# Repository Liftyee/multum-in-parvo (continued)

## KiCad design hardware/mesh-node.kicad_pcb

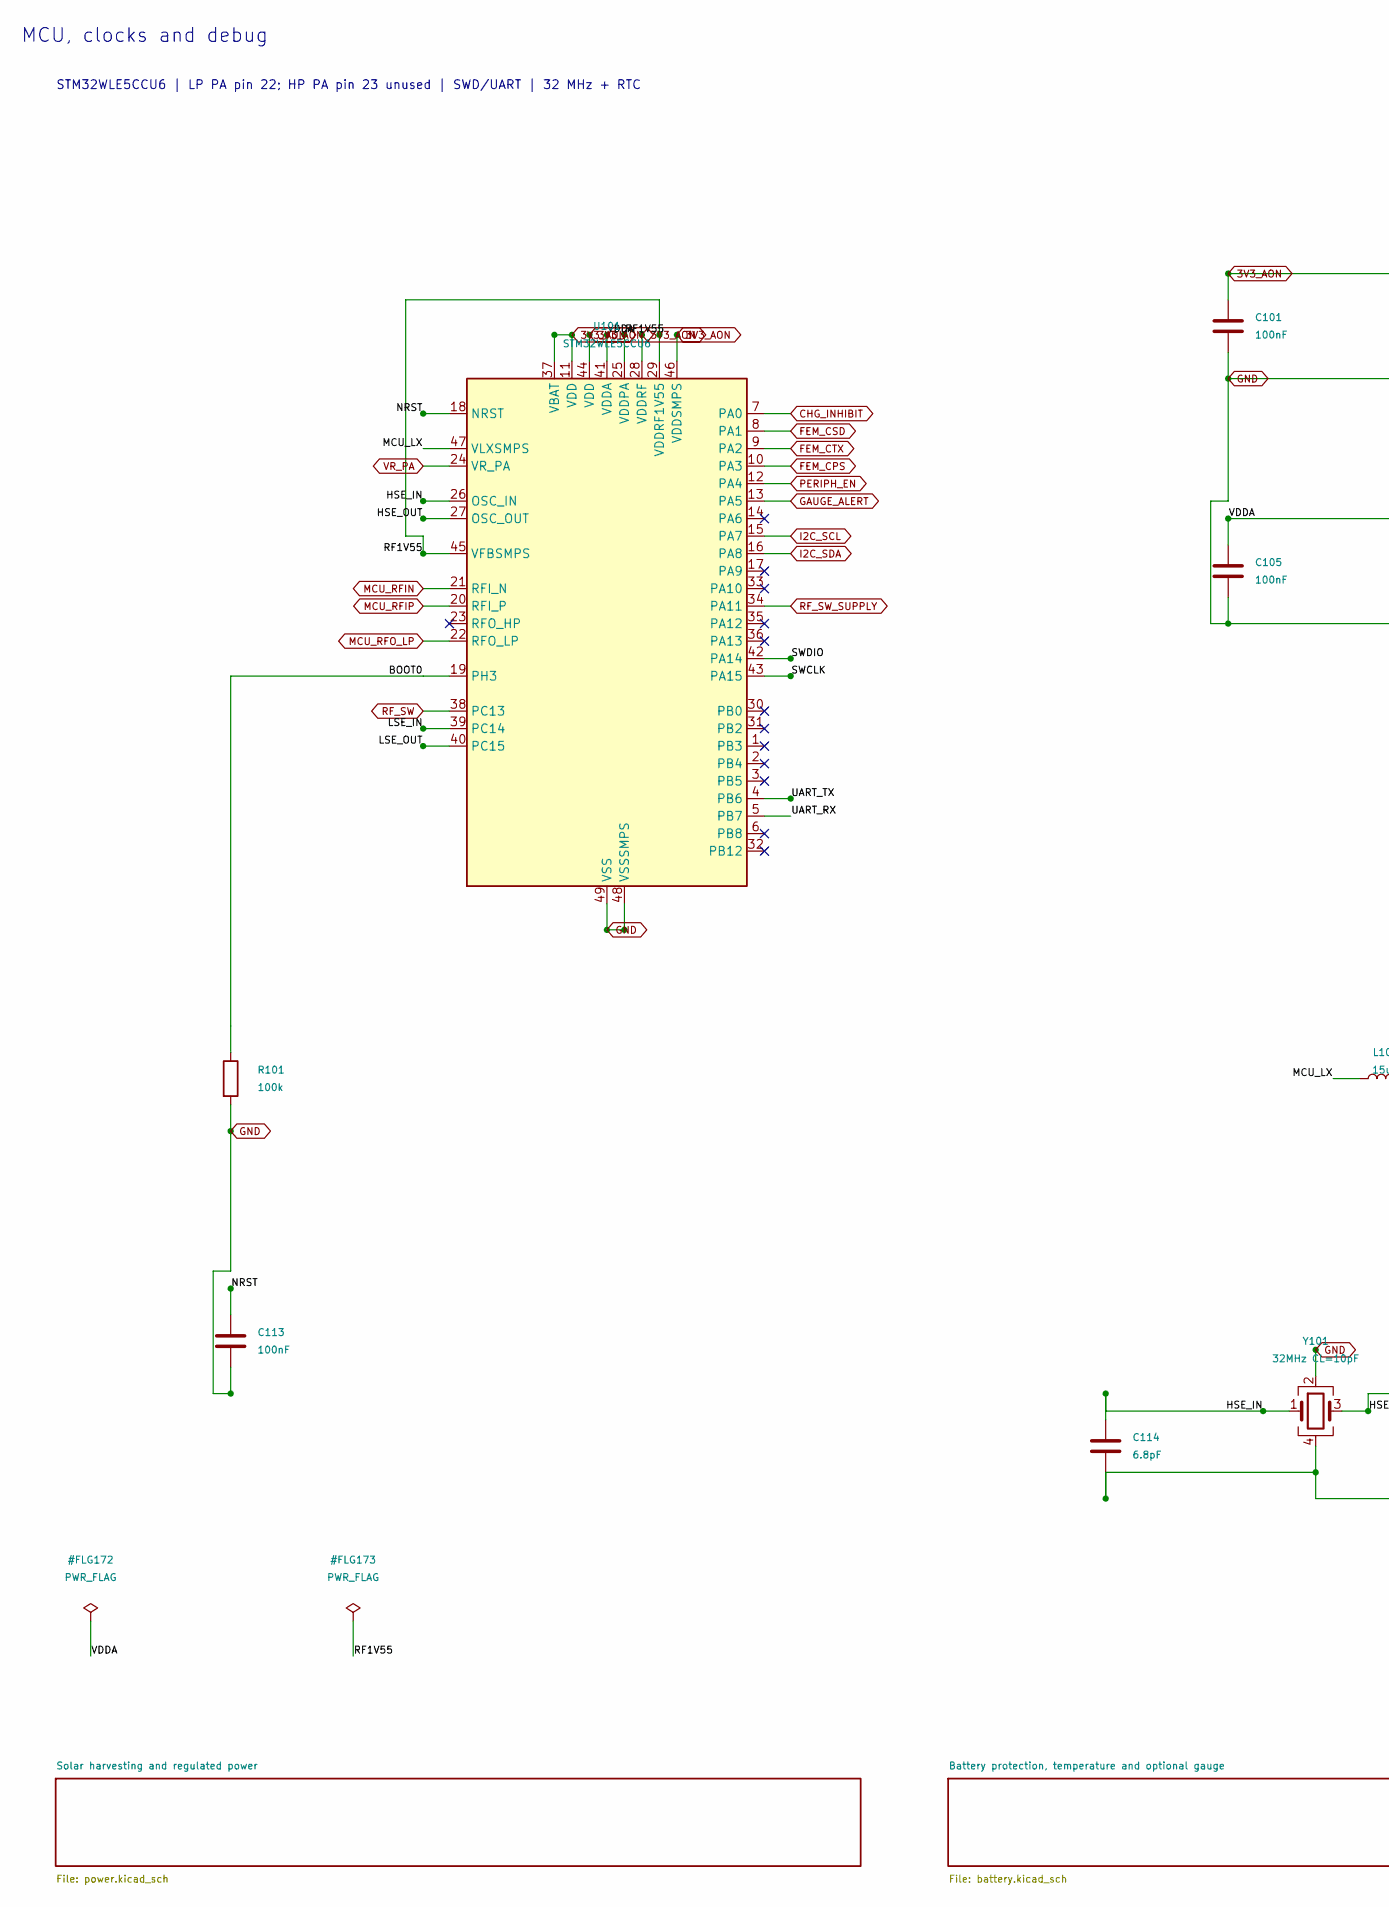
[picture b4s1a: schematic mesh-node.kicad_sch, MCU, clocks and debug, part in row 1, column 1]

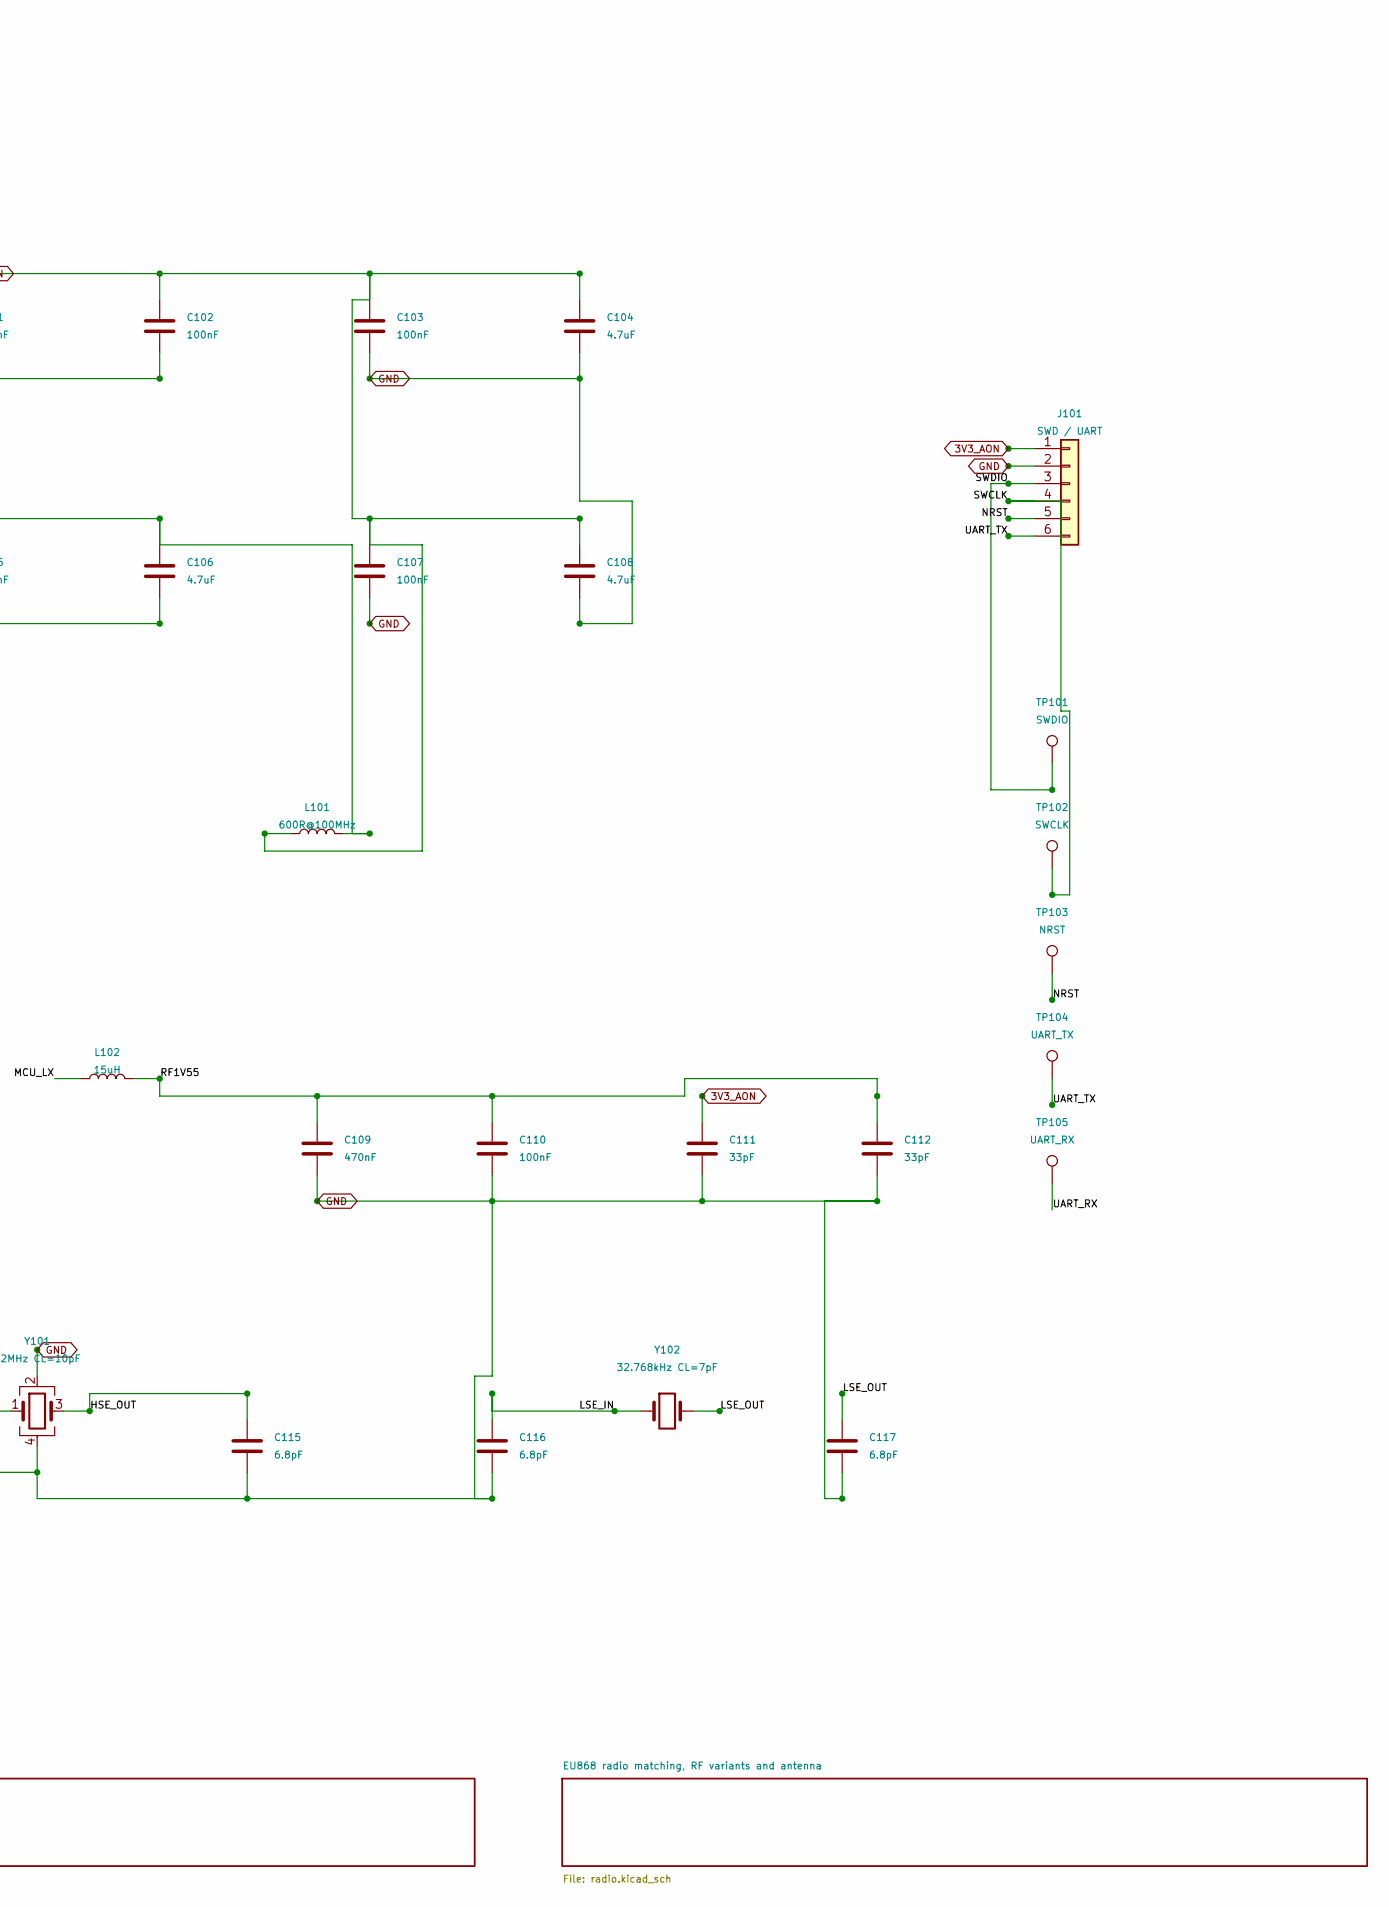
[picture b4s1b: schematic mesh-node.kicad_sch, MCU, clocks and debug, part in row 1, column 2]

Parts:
C101, C102, C103, C105, C107, C110, C113: 100nF; C0603; MPN 100nF
C104, C106, C108: 4.7uF; C0603; MPN 4.7uF
C109: 470nF; C0603; MPN 470nF
C111, C112: 33pF; C0402; MPN 33pF
C114, C115, C116, C117: 6.8pF; C0402; MPN 6.8pF
J101: SWD / UART; Header1x6; MPN SWD / UART
L101: 600R@100MHz; L0603; MPN BLM18AG601SN1D
L102: 15uH; L2520; MPN LQM2MPN150MEHL
R101: 100k; R0603; MPN 100k
TP101: SWDIO; TestPad; MPN SWDIO
TP102: SWCLK; TestPad; MPN SWCLK
TP103: NRST; TestPad; MPN NRST
TP104: UART_TX; TestPad; MPN UART_TX
TP105: UART_RX; TestPad; MPN UART_RX
U101: STM32WLE5CCU6; STM32WLE5_QFN48; MPN STM32WLE5CCU6
Y101: 32MHz CL=10pF; Crystal3225; MPN ABM8-32.000MHZ-10-D1G-T
Y102: 32.768kHz CL=7pF; Crystal3215; MPN ABS07-32.768KHZ-7-T

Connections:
3V3_AON: C101.1, C102.1, C103.1, C104.1, C107.1, C108.1, C111.1, J101.1, L101.1, U101.11 (VDD), U101.28 (VDDRF), U101.37 (VBAT), U101.44 (VDD), U101.46 (VDDSMPS); also elsewhere on the board
/BOOT0: R101.1, U101.19 (PH3)
/HSE_IN: C114.1, U101.26 (OSC_IN), Y101.1
/HSE_OUT: C115.1, U101.27 (OSC_OUT), Y101.3
/LSE_IN: C116.1, U101.39 (PC14), Y102.1
/LSE_OUT: C117.1, U101.40 (PC15), Y102.2
/MCU_LX: L102.1, U101.47 (VLXSMPS)
/NRST: C113.1, J101.5, TP103.1, U101.18 (NRST)
/RF1V55: C109.1, C110.1, C112.1, L102.2, U101.25 (VDDPA), U101.29 (VDDRF1V55), U101.45 (VFBSMPS)
/SWCLK: J101.4, TP102.1, U101.43 (PA15)
/SWDIO: J101.3, TP101.1, U101.42 (PA14)
/UART_RX: TP105.1, U101.5 (PB7)
/UART_TX: J101.6, TP104.1, U101.4 (PB6)
/VDDA: C105.1, C106.1, L101.2, U101.41 (VDDA)
CHG_INHIBIT: U101.7 (PA0); also elsewhere on the board
FEM_CPS: U101.10 (PA3); also elsewhere on the board
FEM_CSD: U101.8 (PA1); also elsewhere on the board
FEM_CTX: U101.9 (PA2); also elsewhere on the board
GAUGE_ALERT: U101.13 (PA5); also elsewhere on the board
GND: C101.2, C102.2, C103.2, C104.2, C105.2, C106.2, C107.2, C108.2, C109.2, C110.2, C111.2, C112.2, C113.2, C114.2, C115.2, C116.2, C117.2, J101.2, R101.2, U101.48 (VSSSMPS), U101.49 (VSS), Y101.2, Y101.4; also elsewhere on the board
I2C_SCL: U101.15 (PA7); also elsewhere on the board
I2C_SDA: U101.16 (PA8); also elsewhere on the board
MCU_RFIN: U101.21 (RFI_N); also elsewhere on the board
MCU_RFIP: U101.20 (RFI_P); also elsewhere on the board
MCU_RFO_LP: U101.22 (RFO_LP); also elsewhere on the board
PERIPH_EN: U101.12 (PA4); also elsewhere on the board
RF_SW: U101.38 (PC13); also elsewhere on the board
RF_SW_SUPPLY: U101.34 (PA11); also elsewhere on the board
VR_PA: U101.24 (VR_PA); also elsewhere on the board

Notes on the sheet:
MCU, clocks and debug
STM32WLE5CCU6 | LP PA pin 22; HP PA pin 23 unused | SWD/UART | 32 MHz + RTC

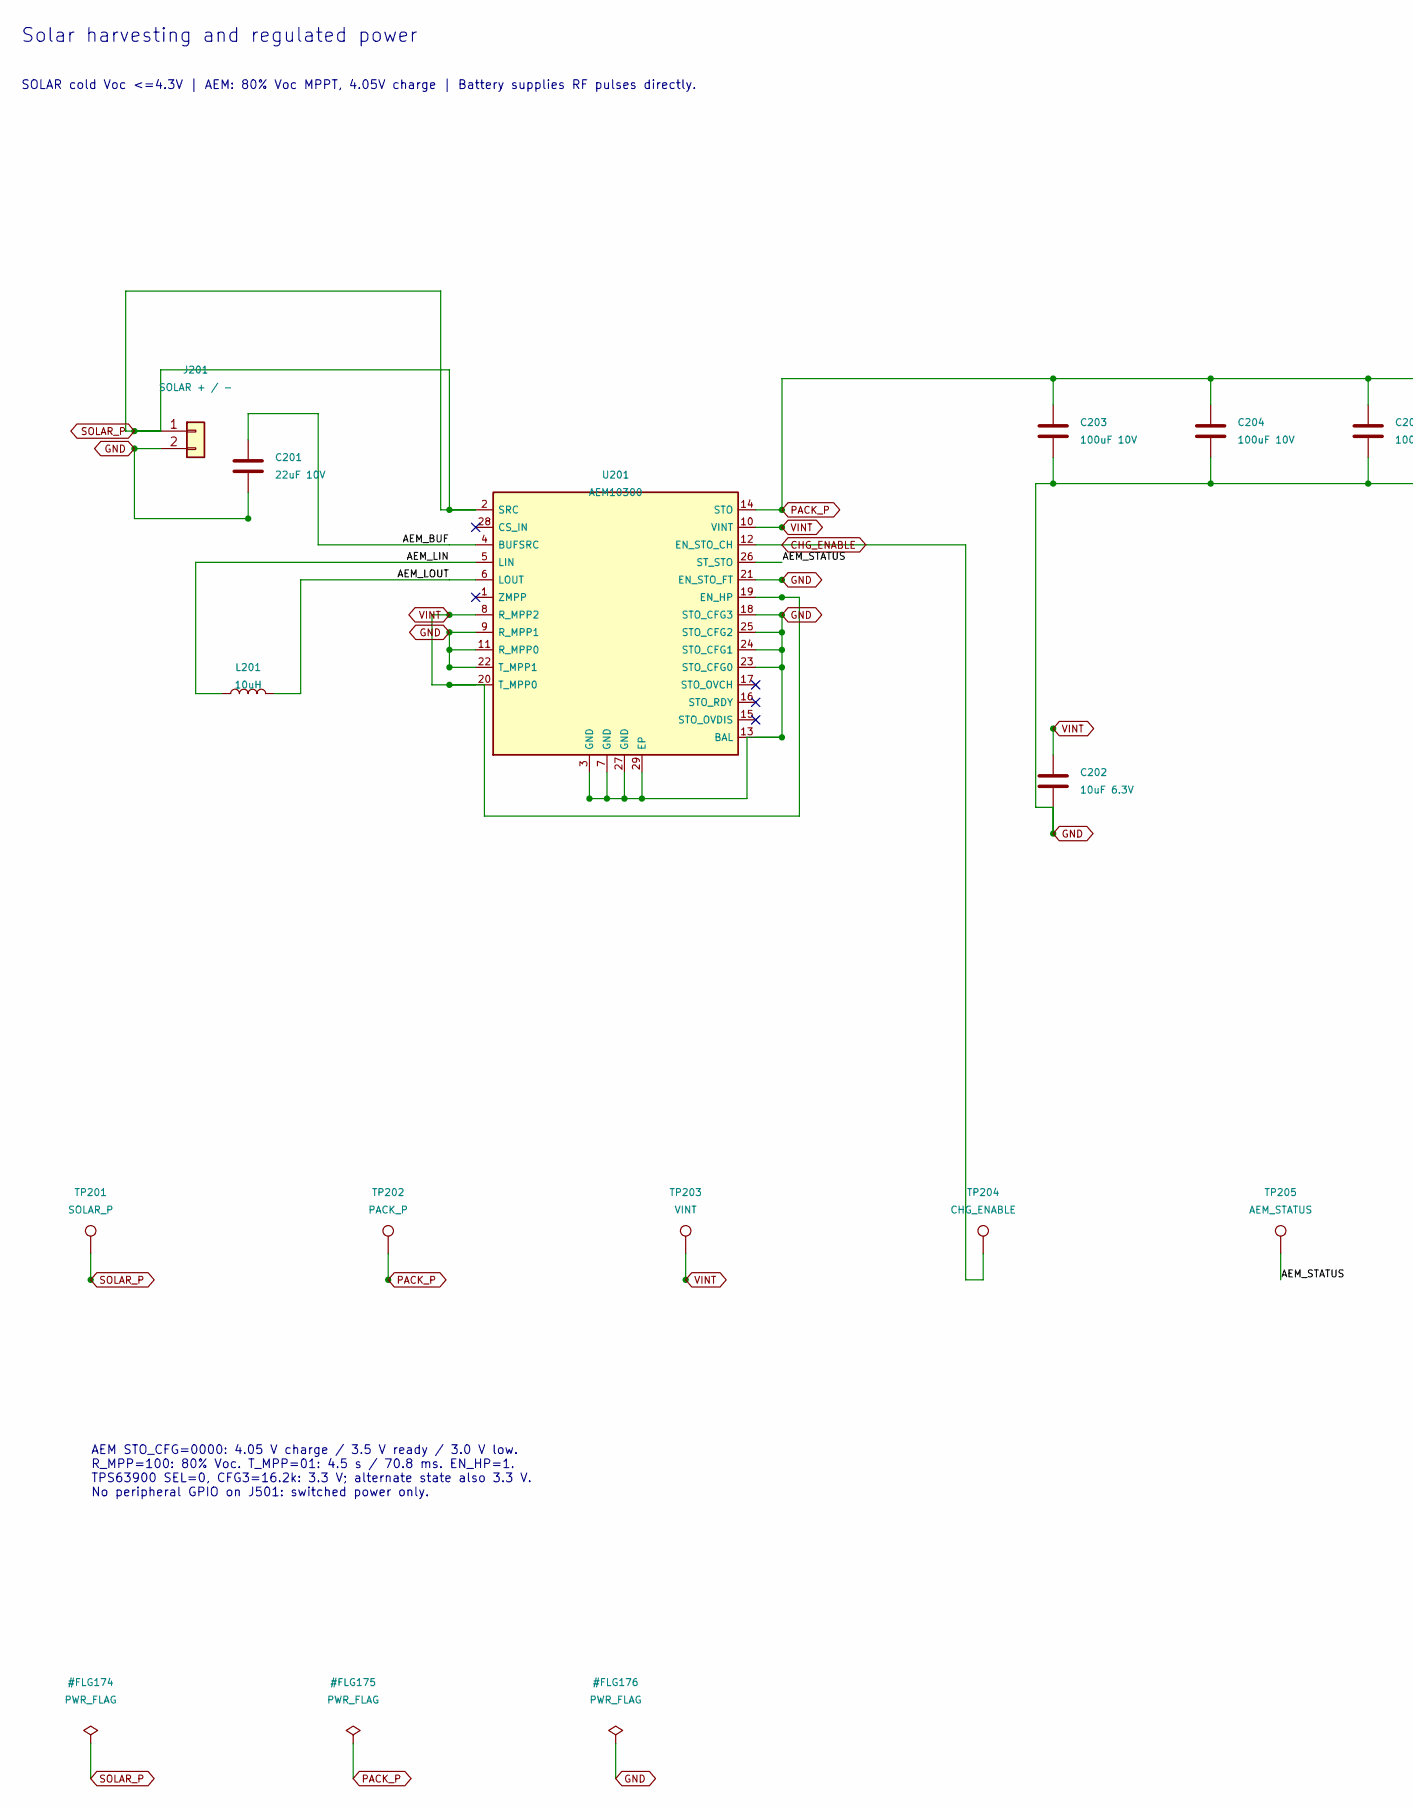
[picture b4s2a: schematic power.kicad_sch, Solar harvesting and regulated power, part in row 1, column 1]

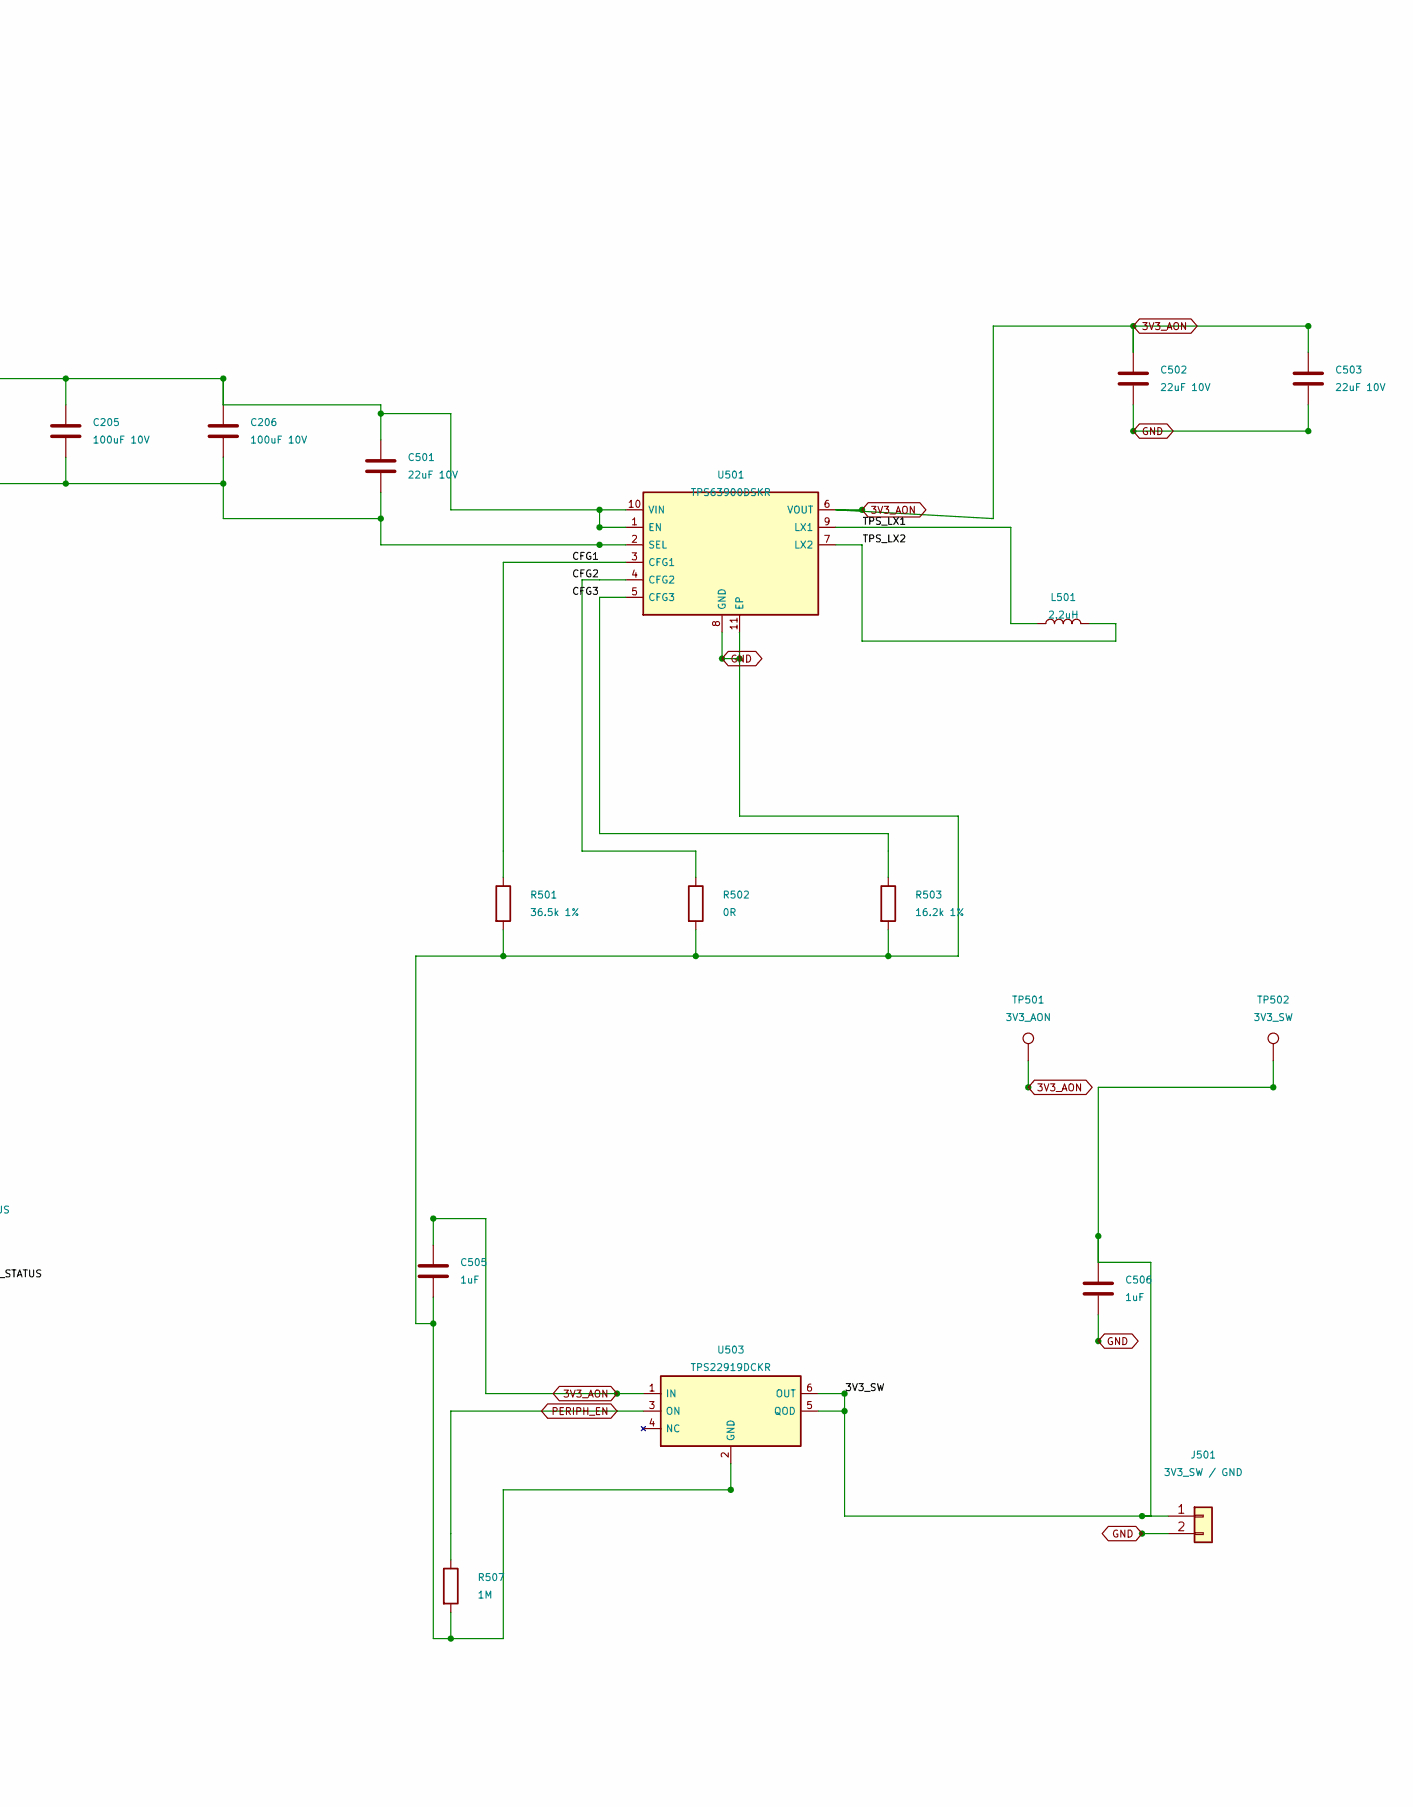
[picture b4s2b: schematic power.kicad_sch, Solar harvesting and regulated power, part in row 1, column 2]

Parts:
C201: 22uF 10V; C0805; MPN GRM21BR61A226ME44L
C202: 10uF 6.3V; C0805; MPN 10uF 6.3V
C203, C204, C205, C206: 100uF 10V; C1210; MPN GRM32ER61A107ME20L
C501, C502, C503: 22uF 10V; C0805; MPN 22uF 10V
C505, C506: 1uF; C0603; MPN 1uF
J201: SOLAR + / -; JST_PH_2; MPN B2B-PH-K-S(LF)(SN)
J501: 3V3_SW / GND; Header1x2; MPN 3V3_SW / GND
L201: 10uH; L2520; MPN DFE252010F-100M
L501: 2.2uH; L2520; MPN DFE252012F-2R2M
R501: 36.5k 1%; R0603; MPN 36.5k 1%
R502: 0R; R0603; MPN 0R
R503: 16.2k 1%; R0603; MPN 16.2k 1%
R507: 1M; R0603; MPN 1M
TP201: SOLAR_P; TestPad; MPN SOLAR_P
TP202: PACK_P; TestPad; MPN PACK_P
TP203: VINT; TestPad; MPN VINT
TP204: CHG_ENABLE; TestPad; MPN CHG_ENABLE
TP205: AEM_STATUS; TestPad; MPN AEM_STATUS
TP501: 3V3_AON; TestPad; MPN 3V3_AON
TP502: 3V3_SW; TestPad; MPN 3V3_SW
U201: AEM10300; AEM10300_QFN28; MPN AEM10300
U501: TPS63900DSKR; TPS63900_WSON10; MPN TPS63900DSKR
U503: TPS22919DCKR; SC70_6; MPN TPS22919DCKR

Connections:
3V3_AON: C502.1, C503.1, C505.1, TP501.1, U501.6 (VOUT), U503.1 (IN); also elsewhere on the board
/Solar harvesting and regulated power/3V3_SW: C506.1, J501.1, TP502.1, U503.5 (QOD), U503.6 (OUT)
/Solar harvesting and regulated power/AEM_BUF: C201.1, U201.4 (BUFSRC)
/Solar harvesting and regulated power/AEM_LIN: L201.1, U201.5 (LIN)
/Solar harvesting and regulated power/AEM_LOUT: L201.2, U201.6 (LOUT)
/Solar harvesting and regulated power/AEM_STATUS: TP205.1, U201.26 (ST_STO)
/Solar harvesting and regulated power/CFG1: R501.1, U501.3 (CFG1)
/Solar harvesting and regulated power/CFG2: R502.1, U501.4 (CFG2)
/Solar harvesting and regulated power/CFG3: R503.1, U501.5 (CFG3)
/Solar harvesting and regulated power/TPS_LX1: L501.1, U501.9 (LX1)
/Solar harvesting and regulated power/TPS_LX2: L501.2, U501.7 (LX2)
CHG_ENABLE: TP204.1, U201.12 (EN_STO_CH); also elsewhere on the board
GND: C201.2, C202.2, C203.2, C204.2, C205.2, C206.2, C501.2, C502.2, C503.2, C505.2, C506.2, J201.2, J501.2, R501.2, R502.2, R503.2, R507.2, U201.3 (GND), U201.7 (GND), U201.9 (R_MPP1), U201.11 (R_MPP0), U201.13 (BAL), U201.18 (STO_CFG3), U201.21 (EN_STO_FT), U201.22 (T_MPP1), U201.23 (STO_CFG0), U201.24 (STO_CFG1), U201.25 (STO_CFG2), U201.27 (GND), U201.29 (EP), U501.2 (SEL), U501.8 (GND), U501.11 (EP), U503.2 (GND); also elsewhere on the board
PACK_P: C203.1, C204.1, C205.1, C206.1, C501.1, TP202.1, U201.14 (STO), U501.1 (EN), U501.10 (VIN); also elsewhere on the board
PERIPH_EN: R507.1, U503.3 (ON); also elsewhere on the board
SOLAR_P: J201.1, TP201.1, U201.2 (SRC); also elsewhere on the board
VINT: C202.1, TP203.1, U201.8 (R_MPP2), U201.10 (VINT), U201.19 (EN_HP), U201.20 (T_MPP0); also elsewhere on the board

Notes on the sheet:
Solar harvesting and regulated power
SOLAR cold Voc <=4.3V | AEM: 80% Voc MPPT, 4.05V charge | Battery supplies RF pulses directly.
AEM STO_CFG=0000: 4.05 V charge / 3.5 V ready / 3.0 V low. R_MPP=100: 80% Voc. T_MPP=01: 4.5 s / 70.8 ms. EN_HP=1. TPS63900 SEL=0, CFG3=16.2k: 3.3 V; alternate state also 3.3 V. No peripheral GPIO on J501: switched power only.
